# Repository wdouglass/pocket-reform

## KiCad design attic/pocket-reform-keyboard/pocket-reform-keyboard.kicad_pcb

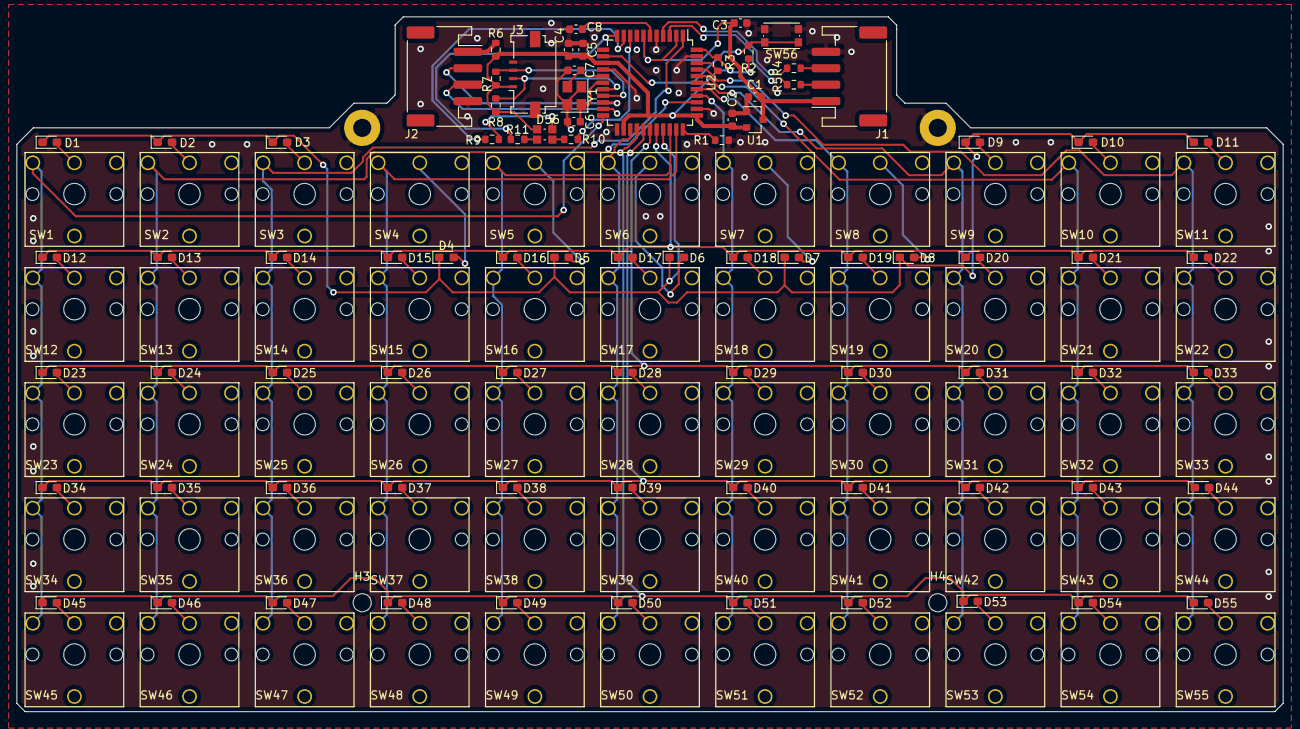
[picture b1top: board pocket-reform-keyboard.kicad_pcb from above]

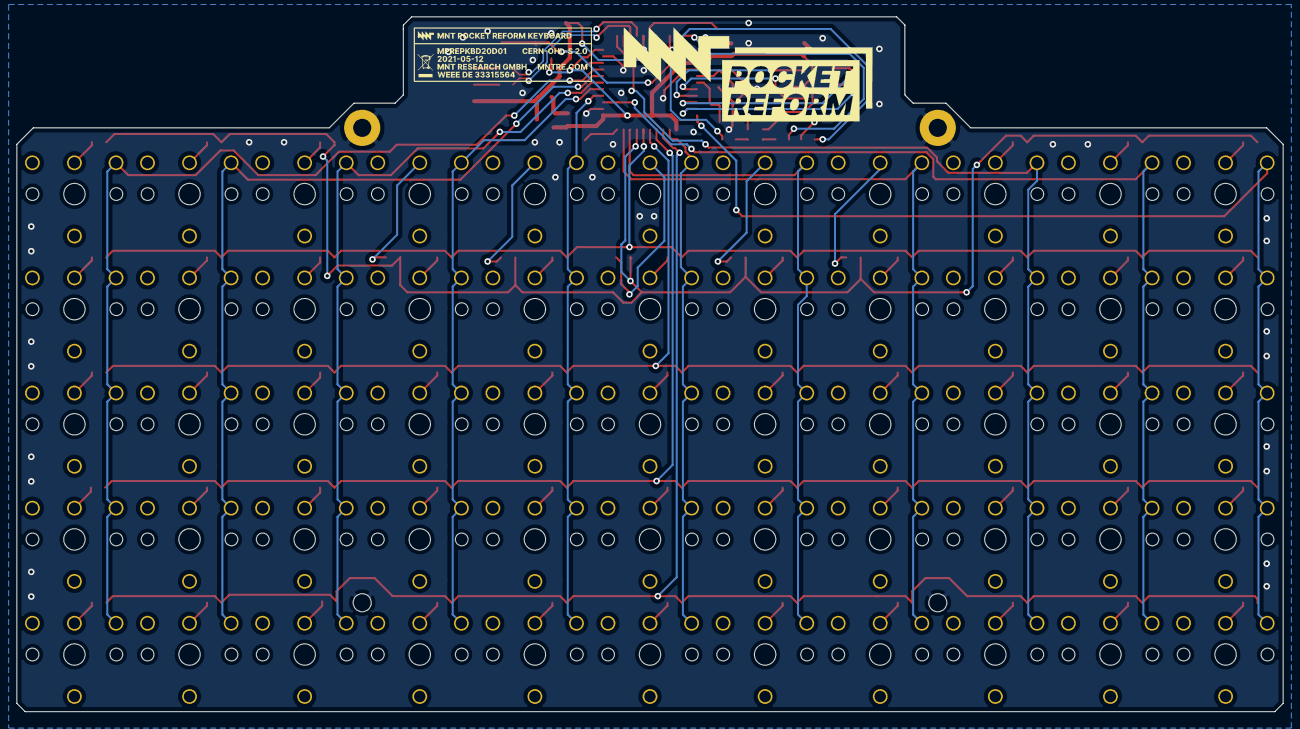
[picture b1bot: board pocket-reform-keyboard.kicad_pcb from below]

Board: 2 copper layers, 154.0 x 84.5 mm, 143 parts (2 on the bottom side), 95 nets.

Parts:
C1, C2, C4, C8: 1uF; C_0603_1608Metric
C3, C5: 0.1uF; C_0603_1608Metric
C6, C7: 18pF; C_0603_1608Metric
D1, D2, D3, D4, D5, D6, D7, D8, D9, D10, D11, D12, D13, D14, D15, D16, D17, D18, D19, D20, D21, D22, D23, D24, D25, D26, D27, D28, D29, D30, D31, D32, D33, D34, D35, D36, D37, D38, D39, D40, D41, D42, D43, D44, D45, D46, D47, D48, D49, D50, D51, D52, D53, D54, D55: MMDL914T1G; D_0603_1608Metric_Pad1.05x0.95mm_HandSolder
D56: LED_RGBA; LED_150080M153000
GFX1: MNT; pocket-reform
GFX2: MNT; mpre-badge-d1
H1: MH1; MountingHole_2.2mm_M2_Pad
H2: MH2; MountingHole_2.2mm_M2_Pad
H3: MH3; MountingHole_2.2mm_M2
H4: MH4; MountingHole_2.2mm_M2
J1: USB; JST_PH_S4B-PH-SM4-TB_1x04-1MP_P2.00mm_Horizontal
J2: UART; JST_PH_S4B-PH-SM4-TB_1x04-1MP_P2.00mm_Horizontal
J3: AUX; Molex_200528-0040_1x04-1MP_P1.00mm_Horizontal
R1, R3, R6: 0; R_0603_1608Metric
R2: 10k; R_0603_1608Metric
R4, R5: 22; R_0603_1608Metric
R7, R8: 4.7k; R_0603_1608Metric
R9: 220; R_0603_1608Metric
R10, R11: 47; R_0603_1608Metric
SW1, SW2, SW3, SW4, SW5, SW6, SW7, SW8, SW9, SW10, SW11, SW12, SW13, SW14, SW15, SW16, SW17, SW18, SW19, SW20, SW21, SW22, SW23, SW24, SW25, SW26, SW27, SW28, SW29, SW30, SW31, SW32, SW33, SW34, SW35, SW36, SW37, SW38, SW39, SW40, SW41, SW42, SW43, SW44, SW45, SW46, SW47, SW48, SW49, SW50, SW51, SW52, SW53, SW54, SW55: Choc; cherry-ml
SW56: RESET; SW_Push_1P1T_NO_CK_KMR2
U1: MCP1700-3302E_SOT23; SOT-23
U2: ATMEGA32U4-AU; TQFP-44_10x10mm_P0.8mm
Y1: 16MHz; Crystal_SMD_3225-4Pin_3.2x2.5mm

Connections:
+3V3: C2.1, C4.1, C5.1, D56.4, J3.1, R2.1, R3.2, R6.2, R7.1, R8.1, U1.2, U2.14, U2.24, U2.34, U2.44
+5V: C1.1, C3.1, J1.1, U1.3, U2.2, U2.7
/Pocket Reform Keyboard MCU/UD+: R4.1, U2.4
/Pocket Reform Keyboard MCU/UD-: R5.1, U2.3
COL1: SW1.1, SW12.1, SW23.1, SW34.1, SW45.1, U2.22
COL2: SW2.1, SW13.1, SW24.1, SW35.1, SW46.1, U2.36
COL3: SW3.1, SW14.1, SW25.1, SW36.1, SW47.1, U2.1
COL4: SW4.1, SW15.1, SW26.1, SW37.1, SW48.1, U2.32
COL5: SW5.1, SW16.1, SW27.1, SW38.1, SW49.1, U2.31
COL6: SW6.1, SW17.1, SW28.1, SW39.1, SW50.1, U2.25
COL7: SW7.1, SW18.1, SW29.1, SW40.1, SW51.1, U2.37
COL8: SW8.1, SW19.1, SW30.1, SW41.1, SW52.1, U2.38
COL9: SW9.1, SW20.1, SW31.1, SW42.1, SW53.1, U2.39
COL10: SW10.1, SW21.1, SW32.1, SW43.1, SW54.1, U2.40
COL11: SW11.1, SW22.1, SW33.1, SW44.1, SW55.1, U2.41
D+: J1.3, R4.2
D-: J1.2, R5.2
DISP_SCL: J3.2, R8.2, U2.18
DISP_SDA: J3.3, R7.2, U2.19
GND: C1.2, C2.2, C3.2, C4.2, C5.2, C6.2, C7.2, C8.2, H1.1, H2.1, H3.1, H4.1, J1.4, J2.4, J3.4, R1.1, SW56.2, U1.1, U2.5, U2.15, U2.23, U2.35, U2.43, Y1.2, Y1.4
unnamed: C6.1, U2.17, Y1.1
unnamed: C7.1, U2.16, Y1.3
unnamed: C8.1, U2.6
unnamed: D1.2, SW1.2
unnamed: D2.2, SW2.2
unnamed: D3.2, SW3.2
unnamed: D4.2, SW4.2
unnamed: D5.2, SW5.2
unnamed: D6.2, SW6.2
unnamed: D7.2, SW7.2
unnamed: D8.2, SW8.2
unnamed: D9.2, SW9.2
unnamed: D10.2, SW10.2
unnamed: D11.2, SW11.2
unnamed: D12.2, SW12.2
unnamed: D13.2, SW13.2
unnamed: D14.2, SW14.2
unnamed: D15.2, SW15.2
unnamed: D16.2, SW16.2
unnamed: D17.2, SW17.2
unnamed: D18.2, SW18.2
unnamed: D19.2, SW19.2
unnamed: D20.2, SW20.2
unnamed: D21.2, SW21.2
unnamed: D22.2, SW22.2
unnamed: D23.2, SW23.2
unnamed: D24.2, SW24.2
unnamed: D25.2, SW25.2
unnamed: D26.2, SW26.2
unnamed: D27.2, SW27.2
unnamed: D28.2, SW28.2
unnamed: D29.2, SW29.2
unnamed: D30.2, SW30.2
unnamed: D31.2, SW31.2
unnamed: D32.2, SW32.2
unnamed: D33.2, SW33.2
unnamed: D34.2, SW34.2
unnamed: D35.2, SW35.2
unnamed: D36.2, SW36.2
unnamed: D37.2, SW37.2
unnamed: D38.2, SW38.2
unnamed: D39.2, SW39.2
unnamed: D40.2, SW40.2
unnamed: D41.2, SW41.2
unnamed: D42.2, SW42.2
unnamed: D43.2, SW43.2
unnamed: D44.2, SW44.2
unnamed: D45.2, SW45.2
unnamed: D46.2, SW46.2
unnamed: D47.2, SW47.2
unnamed: D48.2, SW48.2
unnamed: D49.2, SW49.2
unnamed: D50.2, SW50.2
unnamed: D51.2, SW51.2
unnamed: D52.2, SW52.2
unnamed: D53.2, SW53.2
unnamed: D54.2, SW54.2
unnamed: D55.2, SW55.2
unnamed: D56.1, R9.1
unnamed: D56.2, R10.1
unnamed: D56.3, R11.1
unnamed: J2.1, R6.1
unnamed: R3.1, U2.42
unnamed: R9.2, U2.10
unnamed: R10.2, U2.9
unnamed: R11.2, U2.11
PROG: R1.2, U2.33
RESET: R2.2, SW56.1, U2.13
ROW1: D1.1, D2.1, D3.1, D4.1, D5.1, D6.1, D7.1, D8.1, D9.1, D10.1, D11.1, U2.30
ROW2: D12.1, D13.1, D14.1, D15.1, D16.1, D17.1, D18.1, D19.1, D20.1, D21.1, D22.1, U2.29
ROW3: D23.1, D24.1, D25.1, D26.1, D27.1, D28.1, D29.1, D30.1, D31.1, D32.1, D33.1, U2.28
ROW4: D34.1, D35.1, D36.1, D37.1, D38.1, D39.1, D40.1, D41.1, D42.1, D43.1, D44.1, U2.27
ROW5: D45.1, D46.1, D47.1, D48.1, D49.1, D50.1, D51.1, D52.1, D53.1, D54.1, D55.1, U2.26
UART_RX: J2.2, U2.20
UART_TX: J2.3, U2.21

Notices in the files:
attic/pocket-reform-keyboard/pocket-reform-keyboard.kicad_pcb:
CERN OHL-S 2.0
